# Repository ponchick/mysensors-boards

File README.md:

PCBs designed for MySensors project

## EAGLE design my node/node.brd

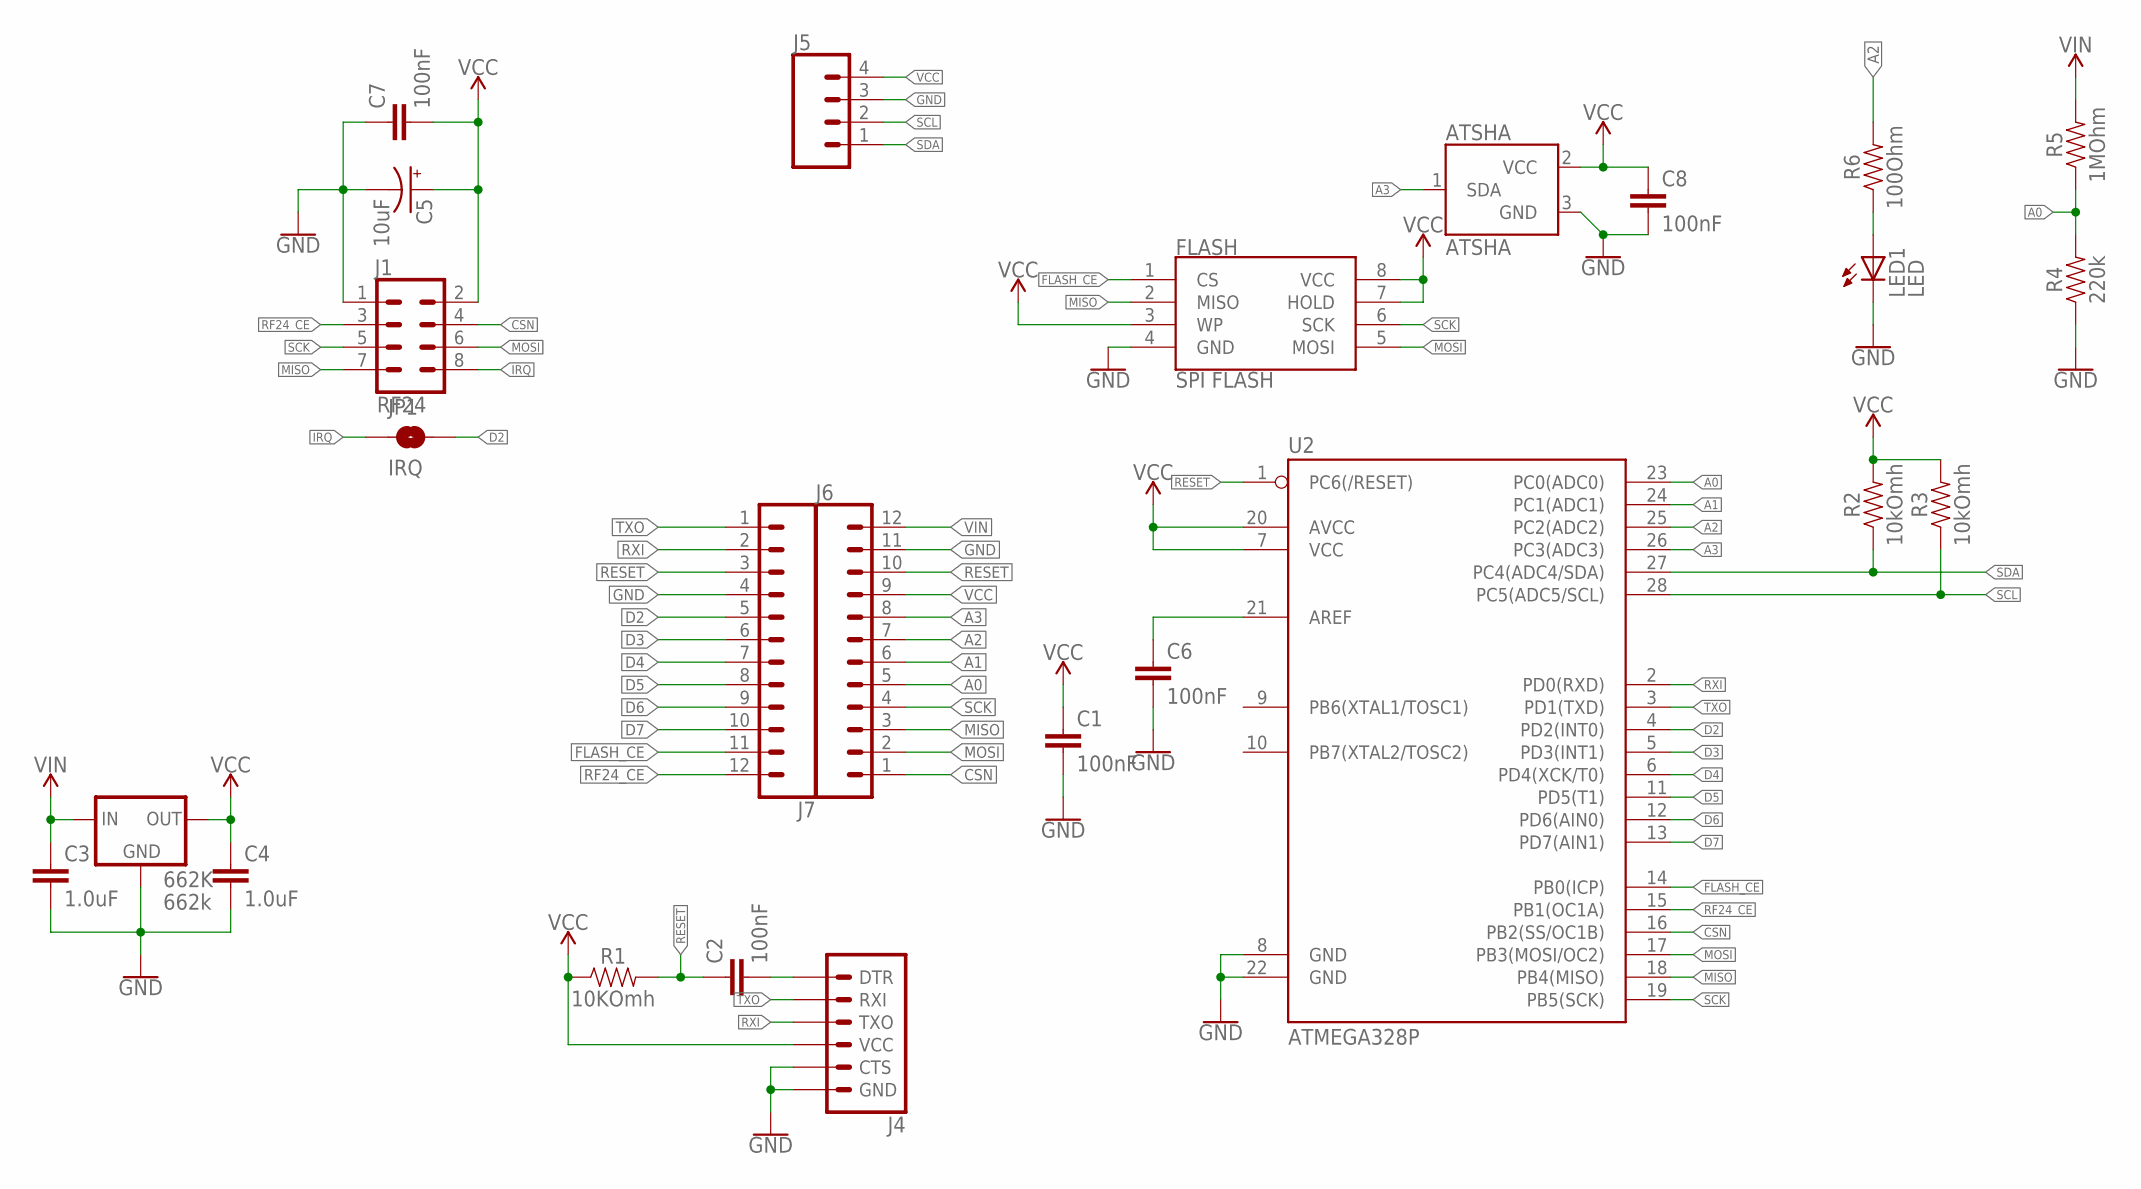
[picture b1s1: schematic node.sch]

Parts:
662K: 662k; SOT23
ATSHA: ATSHA; SOT23-3
C1, C2, C6, C7, C8: 100nF; 0805
C3, C4: 1.0uF; 0805
C5: 10uF; CPOL-RADIAL-2.5MM-5MM
FLASH: SPI FLASH; SO08
J1: RF24; 2X4
J4: 6_PIN_SERIAL_TARGET; 1X06
J5: CONN_04; 1X04
J6, J7: 1X12
JP1: IRQ; SMT-JUMPER_2_NO_NO-SILK
LED1: LED; CHIP-LED0805
R1: 10KOmh; 0805
R2, R3: 10kOmh; 0805
R4: 220k; 0805
R5: 1MOhm; 0805
R6: 100Ohm; 0805
U2: ATMEGA328P; DIP28

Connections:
A0: J6.5, R4.2, R5.1, U2.23 (PC0(ADC0))
A1: J6.6, U2.24 (PC1(ADC1))
A2: J6.7, R6.2, U2.25 (PC2(ADC2))
A3: ATSHA.1 (SDA), J6.8, U2.26 (PC3(ADC3))
CSN: J1.4, J6.1, U2.16 (PB2(SS/OC1B))
D2: J7.5, JP1.2, U2.4 (PD2(INT0))
D3: J7.6, U2.5 (PD3(INT1))
D4: J7.7, U2.6 (PD4(XCK/T0))
D5: J7.8, U2.11 (PD5(T1))
D6: J7.9, U2.12 (PD6(AIN0))
D7: J7.10, U2.13 (PD7(AIN1))
FLASH_CE: FLASH.1 (CS), J7.11, U2.14 (PB0(ICP))
GND: 662K.1 (GND), ATSHA.3 (GND), C1.2, C3.2, C4.2, C5.2 (-), C6.2, C7.1, C8.2, FLASH.4 (GND), J1.1, J4.5 (CTS), J4.6 (GND), J5.3, J6.11, J7.4, LED1.C, R4.1, U2.8 (GND), U2.22 (GND)
IRQ: J1.8, JP1.1
MISO: FLASH.2 (MISO), J1.7, J6.3, U2.18 (PB4(MISO))
MOSI: FLASH.5 (MOSI), J1.6, J6.2, U2.17 (PB3(MOSI/OC2))
unnamed: C2.2, J4.1 (DTR)
unnamed: C6.1, U2.21 (AREF)
unnamed: LED1.A, R6.1
RESET: C2.1, J6.10, J7.3, R1.2, U2.1 (PC6(/RESET))
RF24_CE: J1.3, J7.12, U2.15 (PB1(OC1A))
RXI: J4.3 (TXO), J7.2, U2.2 (PD0(RXD))
SCK: FLASH.6 (SCK), J1.5, J6.4, U2.19 (PB5(SCK))
SCL: J5.2, R3.1, U2.28 (PC5(ADC5/SCL))
SDA: J5.1, R2.1, U2.27 (PC4(ADC4/SDA))
TXO: J4.2 (RXI), J7.1, U2.3 (PD1(TXD))
VCC: 662K.2 (OUT), ATSHA.2 (VCC), C1.1, C4.1, C5.1 (+), C7.2, C8.1, FLASH.3 (WP), FLASH.7 (HOLD), FLASH.8 (VCC), J1.2, J4.4 (VCC), J5.4, J6.9, R1.1, R2.2, R3.2, U2.7 (VCC), U2.20 (AVCC)
VIN: 662K.3 (IN), C3.1, J6.12, R5.2

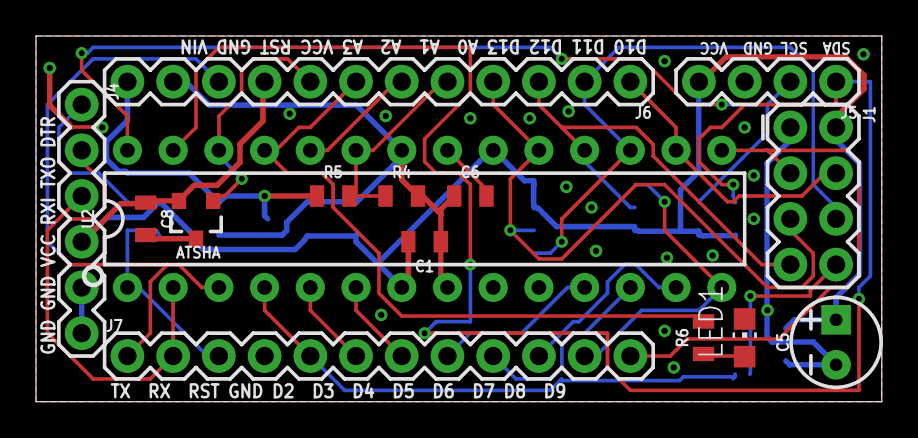
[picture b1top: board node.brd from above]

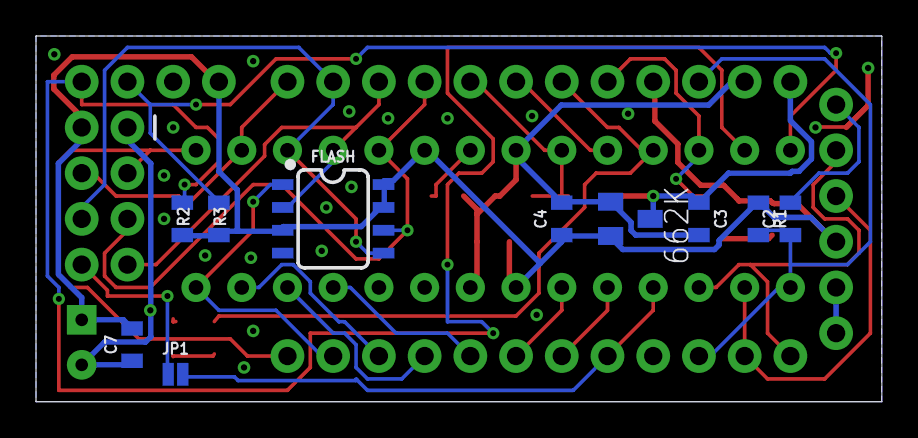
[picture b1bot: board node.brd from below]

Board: 2 copper layers, 47.0 x 20.3 mm, 25 parts (10 on the bottom side), 28 nets.

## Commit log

2017-09-10 Initial
    First version of my node
2017-09-10 Second version
2017-09-10 Third version
    Fixed FTDI connectior
    Pro Mini comatible pinout

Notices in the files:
parts and their libraries:
SparkFun-Connectors: Licensing: Creative Commons ShareAlike 4.0 International - https://creativecommons.org/licenses/by-sa/4.0
